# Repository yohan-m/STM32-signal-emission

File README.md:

STM32-signal-emission
=====================

git repo for the ground STM32 source code

List of folder contains is this repository :
	- Keil project : Emission software
	- Hardware project : Emission PCB

Detailed explanations for each folder :
	- Keil project : STM32-signal-emission
		- Basic : Open the keil project (..\project\p_serverBeacons_stm32F103.uvproj), build all the project, load the executable on the STM32
		- What it does : It controls the emission of four ultrasound beacons.			
		- How it works
			- It creates a PWM connected to the beacons
			- For a period, the PWM have two states : ON and OFF, the duration of states is defined in a header file.
			- You can stop the emission by pressing the button "tamp", relaunch the program with the same button.
			- LED PB8 On : The software had correctly initialized and configured this peripheral.
			- LED PB11 On : The PWM is on.
			- LED PB12 On : The PWN is off.
			- LED PB13 On : The program is stopped.
		- What do you have to modify
			- The duration of the two PWM states (ON and OFF), find defines in the header file "s_beaconSignal.h" (path : ..\include\services)
				- PwmOnPeriod : Duration of the states On (Related to the period of the systick)
				- PwmOffPeriod : Duration of the states Off (Related to the period of the systick)
	- Hardware project : Hardware
		- Basic : Open the eagle project (..\Hardware\Project Eagle Ground Station[emission.pro)
		- What it contains : The PCB for the emission board

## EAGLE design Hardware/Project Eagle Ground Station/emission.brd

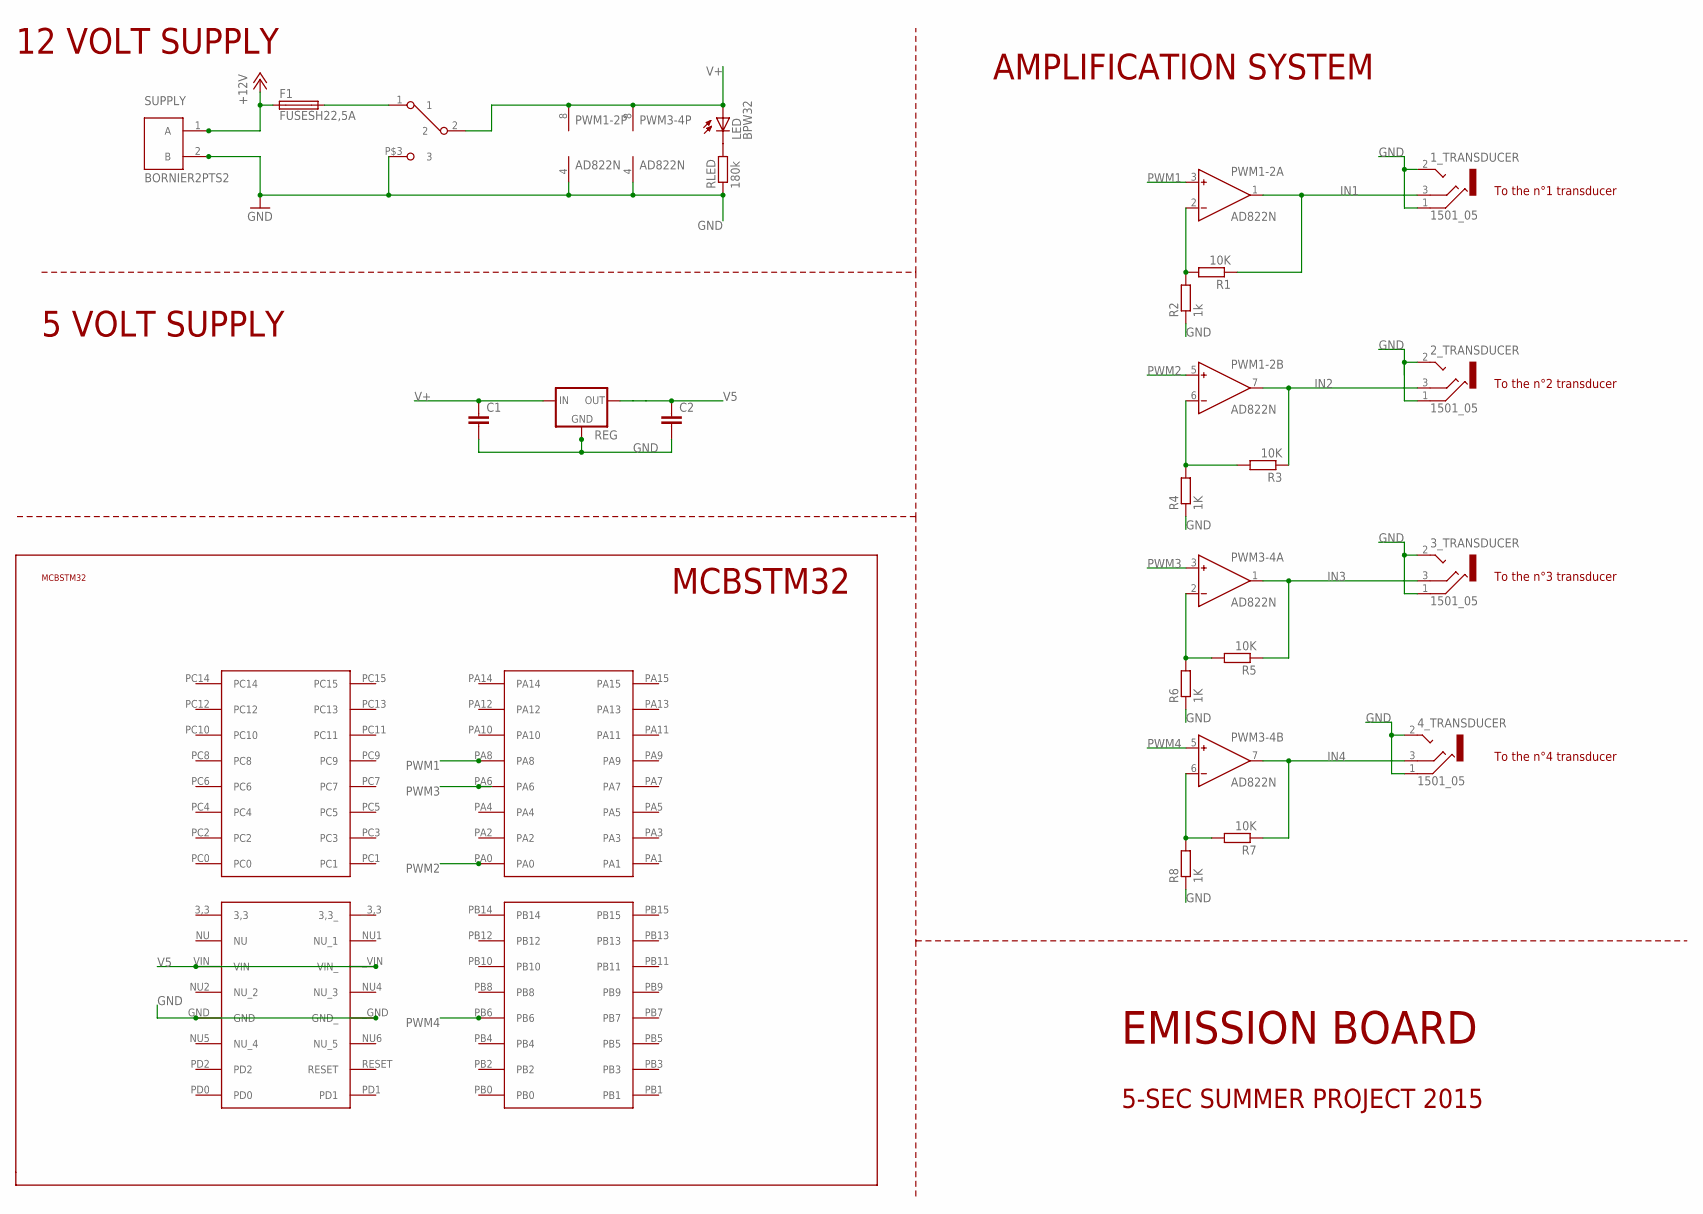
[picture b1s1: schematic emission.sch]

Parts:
1_TRANSDUCER, 2_TRANSDUCER, 3_TRANSDUCER, 4_TRANSDUCER: 1501_05
C1, C2: C-EU050-030X075; C050-030X075
F1: FUSESH22,5A; SH22,5A
LED: BPW32
MCBSTM1: CONNECTOR_MCBSTM32; CONNECTORSTM
PWM1-2, PWM3-4: AD822N; DIL08
R1, R3, R5, R7: 10K; P0613/15
R2: 1k; P0613/15
R4, R6, R8: 1K; P0613/15
REG: 78XXS
RLED: 180k; P0613/15
SUPPLY: BORNIER2PTS2; BORN2X5.08
U$2: SWITCH_CKCOMPONENT

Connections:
+12V: F1.1, SUPPLY.1 (A)
GND: 1_TRANSDUCER.1, 1_TRANSDUCER.2, 2_TRANSDUCER.1, 2_TRANSDUCER.2, 3_TRANSDUCER.1, 3_TRANSDUCER.2, 4_TRANSDUCER.1, 4_TRANSDUCER.2, C1.2, C2.2, MCBSTM1.GND, MCBSTM1._GND (GND_), PWM1-2.4 (V-), PWM3-4.4 (V-), R2.1, R4.1, R6.1, R8.1, REG.GND, RLED.1, SUPPLY.2 (B), U$2.P$3 (3)
IN1: 1_TRANSDUCER.3, PWM1-2.1 (OUT), R1.1
IN2: 2_TRANSDUCER.3, PWM1-2.7 (OUT), R3.1
IN3: 3_TRANSDUCER.3, PWM3-4.1 (OUT), R5.1
IN4: 4_TRANSDUCER.3, PWM3-4.7 (OUT), R7.1
unnamed: PWM1-2.2 (IN-), R1.2, R2.2
unnamed: PWM1-2.6 (IN-), R3.2, R4.2
unnamed: F1.2, U$2.1
unnamed: PWM3-4.2 (IN-), R5.2, R6.2
unnamed: PWM3-4.6 (IN-), R7.2, R8.2
unnamed: LED.K (C), RLED.2
PWM1: MCBSTM1.PA8, PWM1-2.3 (IN+)
PWM2: MCBSTM1.PA0, PWM1-2.5 (IN+)
PWM3: MCBSTM1.PA6, PWM3-4.3 (IN+)
PWM4: MCBSTM1.PB6, PWM3-4.5 (IN+)
V5: C2.1, MCBSTM1.VIN, MCBSTM1._VIN (VIN_), REG.OUT
V+: C1.1, LED.A, PWM1-2.8 (V+), PWM3-4.8 (V+), REG.IN, U$2.2

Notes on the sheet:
AMPLIFICATION SYSTEM
To the n°1 transducer
To the n°2 transducer
To the n°3 transducer
To the n°4 transducer
12 VOLT SUPPLY
5 VOLT SUPPLY
EMISSION BOARD
5-SEC SUMMER PROJECT 2015
MCBSTM32

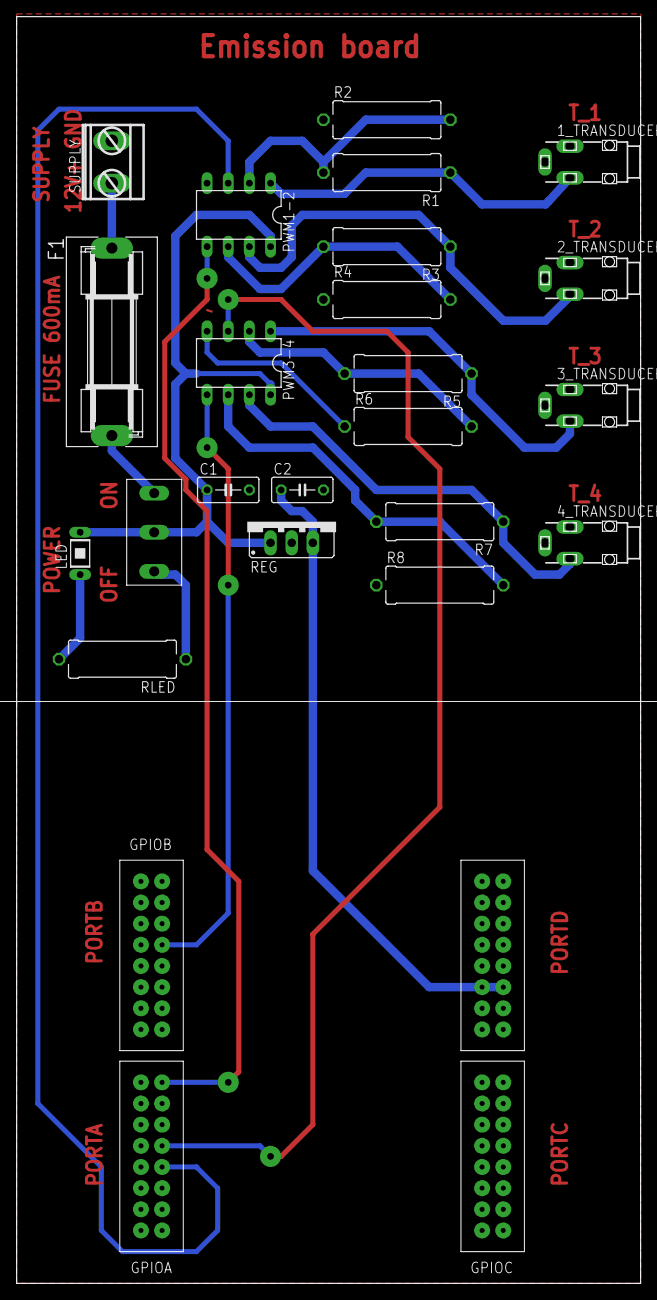
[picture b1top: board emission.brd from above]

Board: 2 copper layers, 74.9 x 152.1 mm, 23 parts (0 on the bottom side), 18 nets.

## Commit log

2014-10-23 added gitignore file
2014-10-31 Ajout du software d'émission
    Ajout de la version 1.0 du software de la station d'émision
2014-10-31 Mis a jour du gitignore
    Refus des fichiers debug
2014-11-02 Commentage (oui ce mot existe !) du code
    Reprise de la logique de codage pour avoir un code plus orienté driver
    service applications et plein de commentaires pour que les attardés de
    l'an prochaine puisse arriver à comprendre un truc
2014-11-02 Bug du précédent commit
    Windows Github c'est de la merde
2014-11-09 Adding comments
2014-11-09 Add the hardware part
2014-11-11 Change the initial state
2014-11-11 Add the readme
2014-11-11 Correct the AOP connection
2015-01-27 Avec le doxygen
